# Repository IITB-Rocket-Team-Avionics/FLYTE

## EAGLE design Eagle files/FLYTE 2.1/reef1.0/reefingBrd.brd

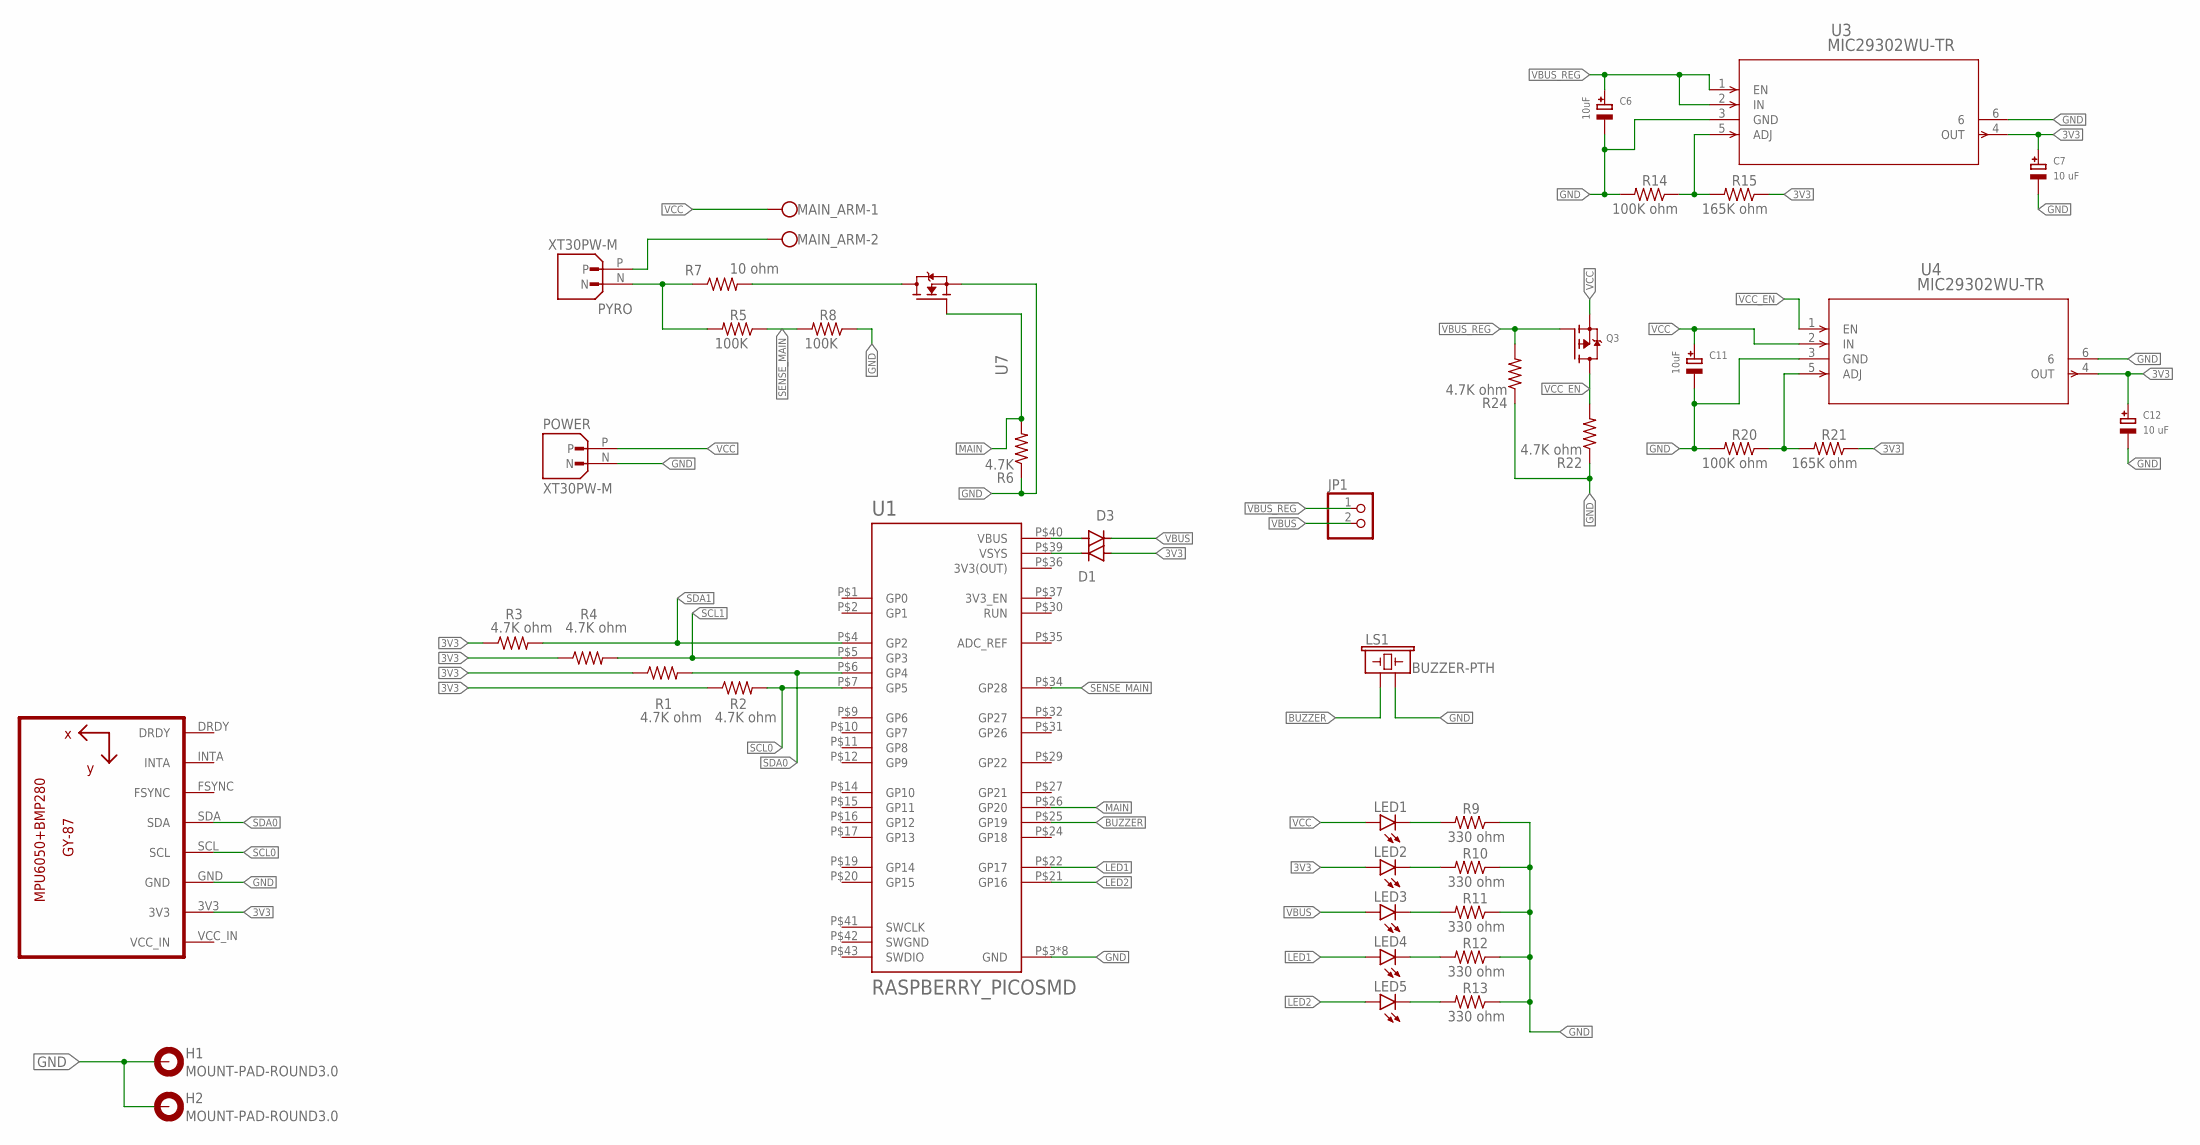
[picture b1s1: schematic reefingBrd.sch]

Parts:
C6, C11: 10uF; EIA3216-18/A-W
C7, C12: 10 uF; EIA3216-18/A-W
D1, D3: 1N4004; DO41-10
H1, H2: MOUNT-PAD-ROUND3.0; 3,0-PAD
JP1: PINHD-1X2; 1X02
LED1, LED2, LED3, LED4, LED5: LEDCHIPLED_1206; CHIPLED_1206
LS1: BUZZER-PTH; BUZZER-12MM
MAIN_ARM: W237-102
POWER: XT30PW-M; AMASS_XT30PW-M
PYRO: XT30PW-M; AMASS_XT30PW-M
Q3: MOSFET-PWIDE; SOT23-WIDE
R1, R2, R3, R4, R22, R24: 4.7K ohm; R0805
R5, R8: 100K; R0805
R6: 4.7K; R0805
R7: 10 ohm; 0207/10
R9, R10, R11, R12, R13: 330 ohm; R0805
R14, R20: 100K ohm; R0805
R15, R21: 165K ohm; R0805
U1: RASPBERRY_PICOSMD; PICO-PKG-SMD
U2: GY-521MPU6050; GY-521
U3, U4: MIC29302WU-TR; TO-263-5_MCH
U7: IRF540NPBF; TO254P1054X469X1930-3

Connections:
3V3: C7.+, C12.+, D1.A, LED2.A, R1.1, R2.1, R3.1, R4.1, R15.1, R21.1, U2.3V3, U3.4 (OUT), U4.4 (OUT)
3V3(OUT): U1.P$36 (3V3(OUT))
BUZZER: LS1.+ (1), U1.P$25 (GP19)
GND: C6.-, C7.-, C11.-, C12.-, H1.B3,0, H2.B3,0, LS1.- (2), POWER.N, R6.1, R8.1, R9.1, R10.1, R11.1, R12.1, R13.1, R14.2, R20.2, R22.1, R24.1, U1.P$3 (GND), U1.P$8 (GND), U1.P$13 (GND), U1.P$18 (GND), U1.P$23 (GND), U1.P$28 (GND), U1.P$33 (GND), U1.P$38 (GND), U2.GND, U3.3 (GND), U3.6, U4.3 (GND), U4.6, U7.3 (S)
LED1: LED4.A, U1.P$22 (GP17)
LED2: LED5.A, U1.P$21 (GP16)
MAIN: R6.2, U1.P$26 (GP20), U7.1 (G)
unnamed: D1.C, U1.P$39 (VSYS)
unnamed: D3.A, U1.P$40 (VBUS)
unnamed: R20.1, R21.2, U4.5 (ADJ)
unnamed: PYRO.N, R5.2, R7.1
unnamed: R7.2, U7.2 (D)
unnamed: MAIN_ARM.2, PYRO.P
unnamed: R14.1, R15.2, U3.5 (ADJ)
unnamed: LED1.C, R9.2
unnamed: LED2.C, R10.2
unnamed: LED3.C, R11.2
unnamed: LED4.C, R12.2
unnamed: LED5.C, R13.2
SCL0: R2.2, U1.P$7 (GP5), U2.SCL
SCL1: R4.2, U1.P$5 (GP3)
SDA0: R1.2, U1.P$6 (GP4), U2.SDA
SDA1: R3.2, U1.P$4 (GP2)
SENSE_MAIN: R5.1, R8.2, U1.P$34 (GP28)
SWGND: U1.P$42 (SWGND)
VBUS: D3.C, JP1.2, LED3.A
VBUS_REG: C6.+, JP1.1, Q3.1 (G), R24.2, U3.1 (EN), U3.2 (IN)
VCC: C11.+, LED1.A, MAIN_ARM.1, POWER.P, Q3.2 (S), U4.2 (IN)
VCC_EN: Q3.3 (D), R22.2, U4.1 (EN)

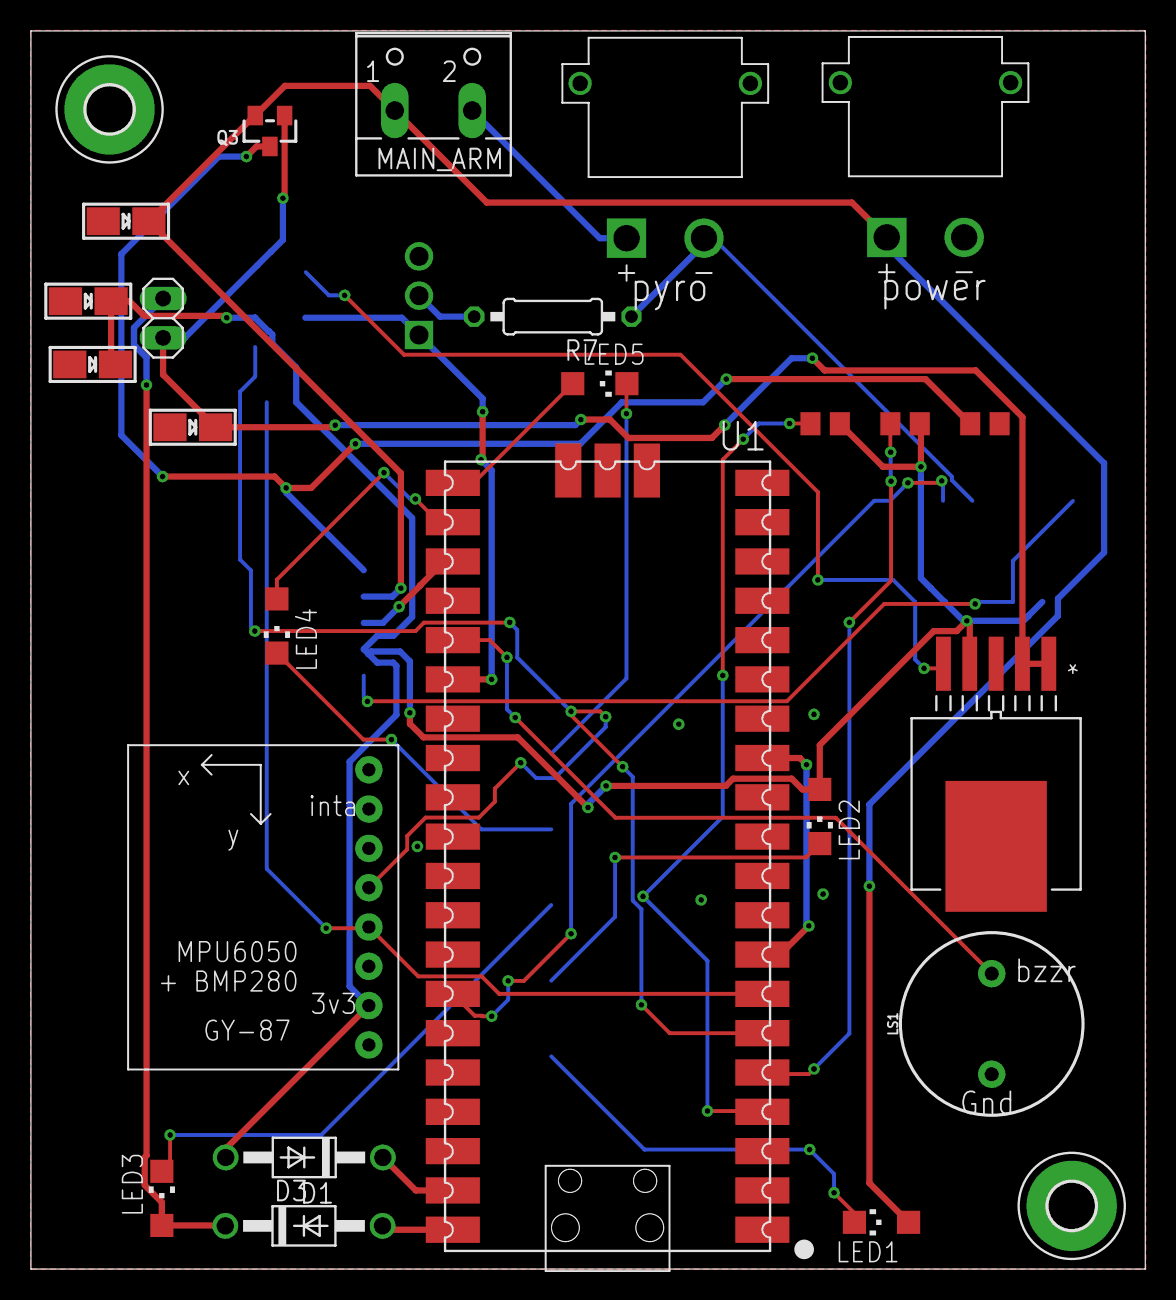
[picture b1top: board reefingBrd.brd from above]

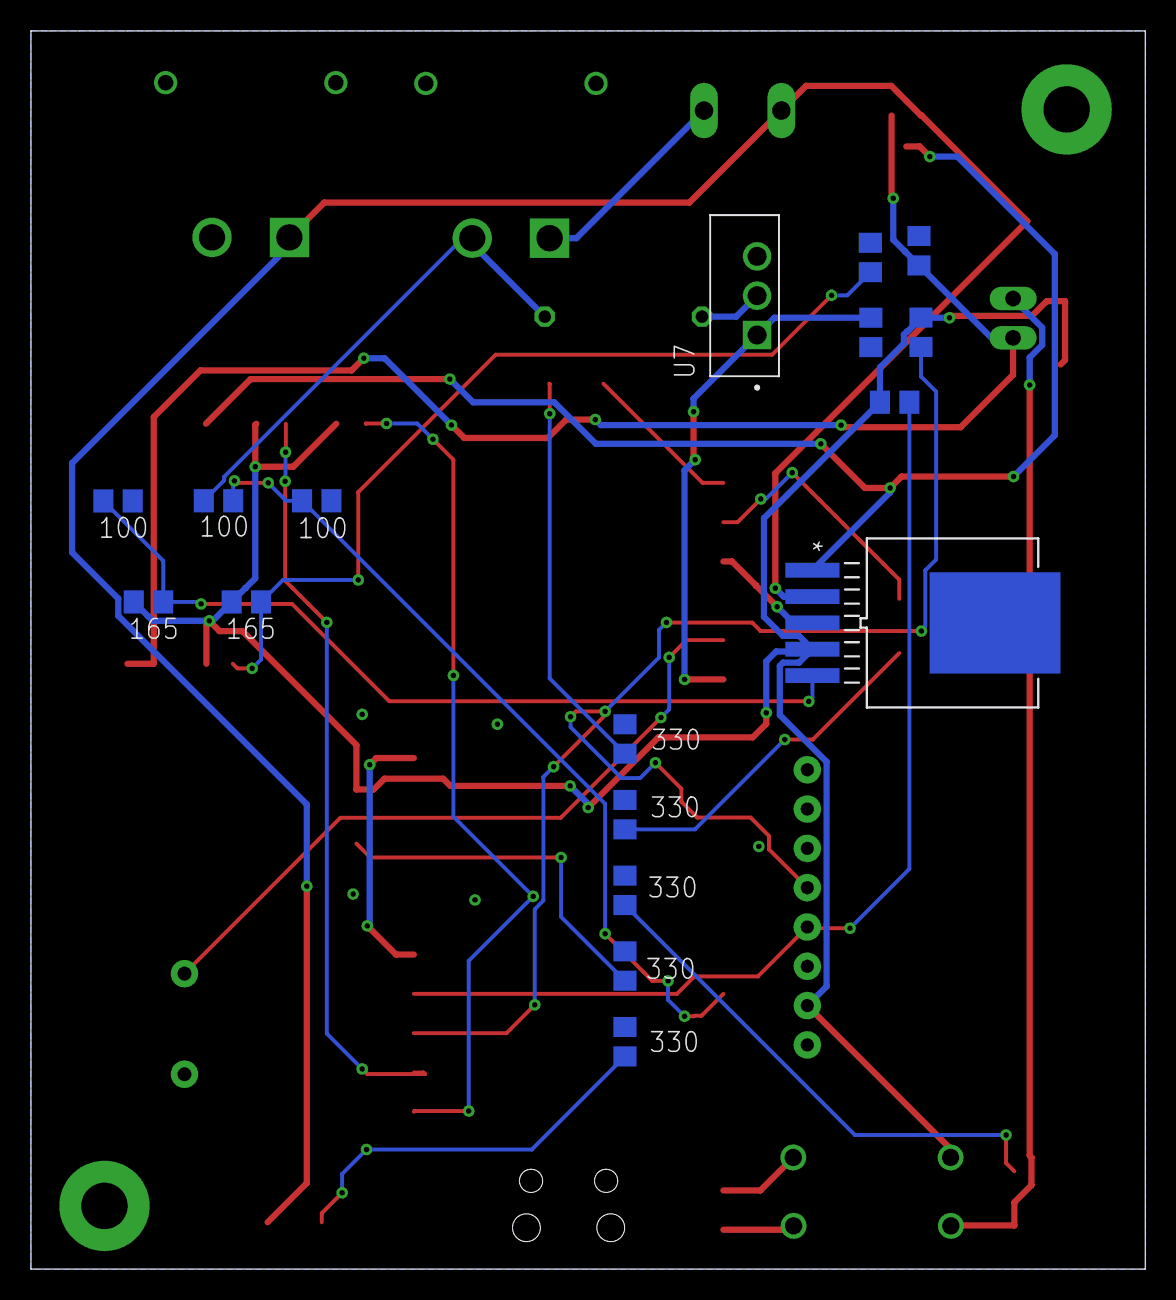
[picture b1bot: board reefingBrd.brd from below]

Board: 2 copper layers, 72.0 x 80.0 mm, 43 parts (17 on the bottom side), 27 nets.

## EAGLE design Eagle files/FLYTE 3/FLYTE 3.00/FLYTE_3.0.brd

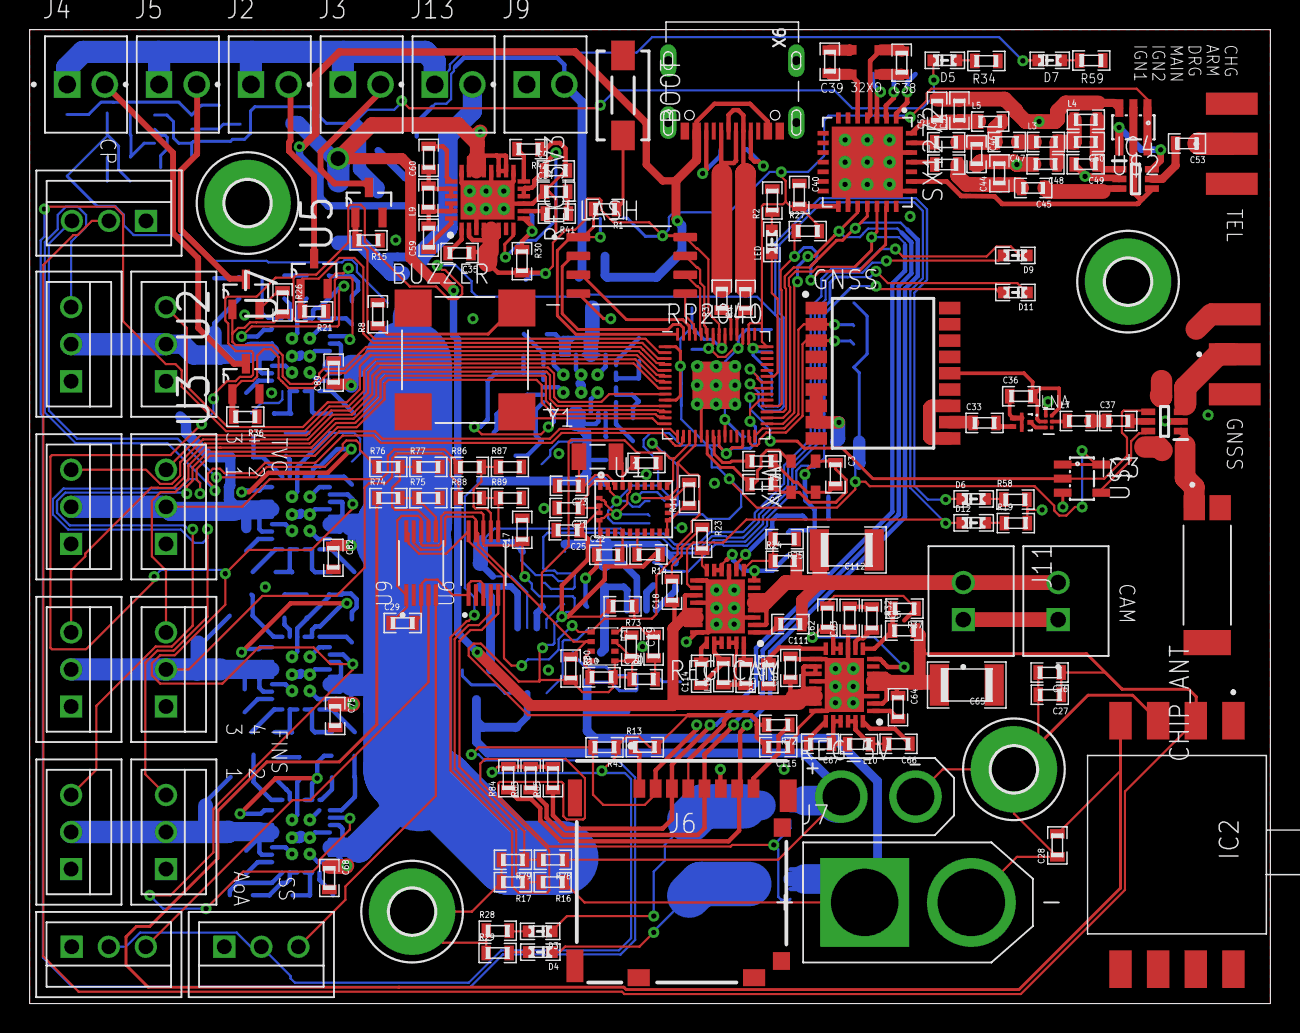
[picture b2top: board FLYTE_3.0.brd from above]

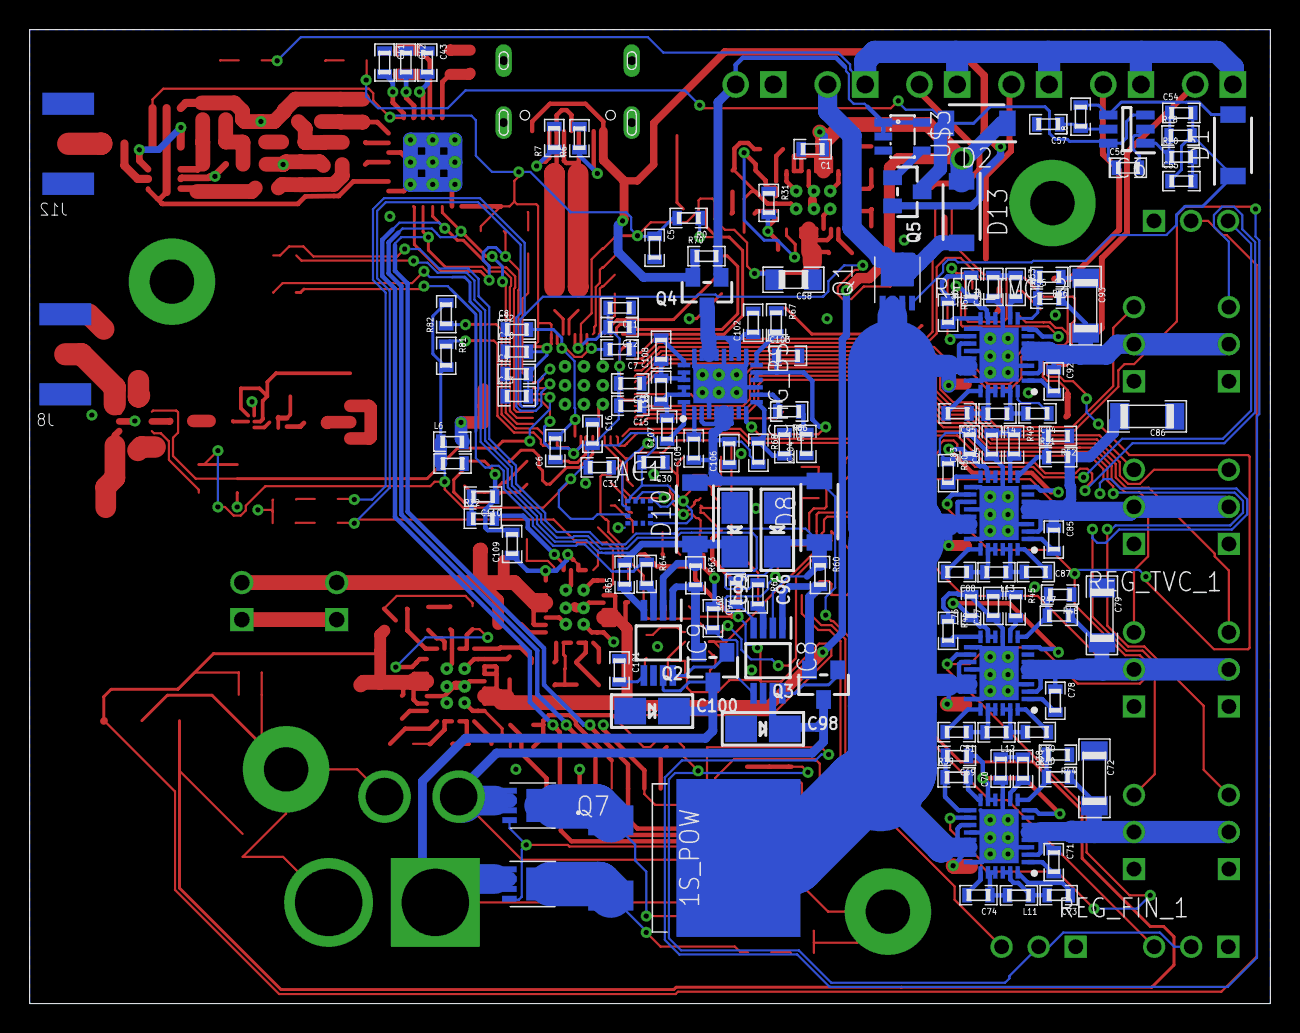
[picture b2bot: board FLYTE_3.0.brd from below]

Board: 2 copper layers, 83.7 x 65.7 mm, 307 parts (129 on the bottom side), 222 nets.

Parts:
1S_POW: V60D60C-M3_I; V60D60CM3I
32XO: ASE
AC1: KX134-1211; KX1341211
AOA: 03-JST-B3B-XH-A; B3B-XH
BOOT: DTSM-3
BUZZER: BUZZER; CUI_CMT-8530S-SMT
C1, C18, C61, C68, C75, C82, C89, C102, C106: 10 uF; 0603
C2, C3, C38, C39: 24 pF; 0603
C4, C57, C62, C69, C76, C83, C90, C103, C109: 4.7 uF; 0603
C5, C6, C7, C9, C11, C12, C13, C14, C15, C16, C19, C20, C21, C22, C25, C40, C41, C42, C43: 100 nF; 0603
C8, C10, C26, C55, C56, C115: 1 uF; 0603
C17, C29, C30, C31, C97, C101: 0.1 uF; 0603
C23, C24: 25 pF; 0603
C27, C32, C51: 10 nF; 0603
C28: 470 pF; 0603
C33, C37: 120 pF; 0603
C34: 3.3 nF; 0603
C35, C64, C71, C78, C85, C92, C105, C111: 22 nF; 0603
C36: 1 nF; 0603
C44, C49: 3.3 pF; 0603
C45, C52, C53: 47 pF; 0603
C46, C48: 8.2 pF; 0603
C47: 22 pF; 0603
C50: 1.5 pF; 0603
C54: 10 pF; 0603
C58: 100 uF; 0805
C59, C60, C66, C67, C73, C74, C80, C81, C87, C88, C94, C95, C107, C108, C113, C114: 0.22 uF; 0603
C63, C70, C77, C84, C91, C110: 1.8 nF; 0603
C65: 220 uF; 1210
C72, C79, C86, C93: 100 uF; 1206
C96, C98, C99, C100: 10uF; EIA3216-18/A-W
C104: 1.2 nF; 0603
C112: 100 uF; 1210
CHG_BST: LT3120JV#PBF; QFN50P400X500X83-29N
CHIP_ANT: W3010; XCVR_W3010
D1, D2, D8, D10, D13: RSX501LAM20TR; SODFL4725X105N
D3, D4, D5, D6, D7, D9, D11, D12: 0603.LED
FIN_1, FIN_2, FIN_3, FIN_4: 03-JST-B3B-XH-A; B3B-XH
FLASH: W25Q128JVSIQ; SOIC127P790X216-8N
GNSS: TESEO-LIV3F; SON110P970X1010X230-18N
H1, H2, H3, H4: MOUNT-PAD-ROUND3.0; 3,0-PAD
IC1: BMP280
IC2: MPXV5100DP
IC3, IC4: AS179-92LF; SOT65P220X100-6N
IC6: MAX8574EUT+T; SOT95P280X145-6N
IC8: MCP73843-420I_MS; SOP65P490X110-8N
IC9: MCP73844-840I_MS; SOP65P490X110-8N
J2, J3, J4, J5, J9, J13: 282834-2; TE_282834-2
J6: 503182-1852; 5031821852
J7: XT60-M; AMASS_XT60-M
J8, J12: CON-SMA-EDGE-S; RFSOLUTIONS_CON-SMA-EDGE-S
J10, J11: B2B-XH-A(LF)(SN); JST_B2B-XH-A(LF)(SN)
L1: 10 nH; 0603
L2: 2.7 nH; 0603
L3, L4, L7: 5.6 nH; 0603
L5: 33 nH; 0603
L6: 27 nH; 0603
L8: 22 uH; 0603
L9, L10, L11, L12, L13, L14, L15, L16: 4.7 uH; 0603
LED: 0603.LED
LNA: BGA725L6; AMP_BGA725L6E6327FTSA1
MOTOR: 03-JST-B3B-XH-A; B3B-XH
Q1, Q6, Q7: SI7625DN-T1-GE3; SIS862DNT1GE3
Q2, Q3, Q4, Q5: SOT23-WIDE
R0, R9, R10, R13, R15, R20, R21, R26, R27, R36, R43, R70, R72, R73, R80, R81, R82, R83, R84, R85: 10k ohm; 0603
R1, R5: 1k ohm; 0603
R2, R19, R58: 60 ohm; 0603
R3, R4: 27.4 ohm; 0603
R6, R7: 5.1k ohm; 0603
R8: 100 ohm; 0603
R11, R14: 10 kohm; 0603
R16: 412k ohm; 0603
R17, R25, R31, R37, R62, R65, R66, R69, R75, R77, R79, R87, R89: 100k ohm; 0603
R18: 137k ohm; 0603
R22, R32, R38, R45, R49, R53: 46.4k ohm; 0603
R23, R33, R39, R42, R46, R50, R54, R67, R86, R88: 158k ohm; 0603
R24, R35: 523k ohm; 0603
R28: 105 ohm; 0603
R29, R59: 315 ohm; 0603
R30: 316k ohm; 0603
R34, R61, R64: 158 ohm; 0603
R40, R47, R51, R55: 402k ohm; 0603
R41: 21k ohm; 0603
R44, R48, R52, R56: 50k ohm; 0603
R60, R63: 0.1 ohm; 0603
R68: 1.3M ohm; 0603
R74: 36.5k ohm; 0603
R76: 43k ohm; 0603
R78: 28k ohm; 0603
REG_3V3, REG_5V: LT3120JV#PBF; QFN50P400X500X83-29N
REG_CAM: LT3120JV#PBF; QFN50P400X500X83-29N
REG_FIN_1, REG_FIN_2: LT3120JV#PBF; QFN50P400X500X83-29N
REG_TVC_1, REG_TVC_2: LT3120JV#PBF; QFN50P400X500X83-29N
RP2040: RP2040-QFN56; RP2040-QFN-56
SAW: SAW_FILTER; FIL_AFS14A04-1575.42-T3
SS: 03-JST-B3B-XH-A; B3B-XH
SX1272: SX1272IMLTRT; QFN65P600X600X100-29N
TVC_1, TVC_2, TVC_3, TVC_4: 03-JST-B3B-XH-A; B3B-XH
U1: BNO055; LGA28R50P4X10_380X520X100
U2, U3, U5, U7: CJ3400; SOT91P240X120-3N
U6, U9: ADS1115IDGSR; SOP50P490X110-10N
U$1, U$2, U$3: SN74LVC1G04DBVR; SOT23-5
U$11: XT30UPB-M
X6: USB Type C; USB_C_CUSB31-CFM2AX-01-X
XTAL: ASE
Y1: FC-135_32.7680KA-A0; XTAL_FC-135_32.7680KA-A0

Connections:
1S_ADC: R78.2, R79.1, U6.5
1S_POW: 1S_POW.1, D3.P$1, Q7.5, Q7.6, Q7.7, Q7.8, Q7.9, Q7.10, Q7.11
1V1: C6.2, C7.2, C8.2, RP2040.23, RP2040.45, RP2040.50
2S_ADC: R16.2, R17.1, U6.4
2S_POW: 1S_POW.2, D4.P$1, Q6.5, Q6.6, Q6.7, Q6.8, Q6.9, Q6.10, Q6.11
3V3: AC1.1, AC1.3, AC1.7, AC1.10, AOA.P$2, C5.1, C9.2, C10.2, C11.2, C12.2, C13.2, C14.2, C15.2, C16.2, C17.1, C19.2, C20.1, C21.1, C25.1, C29.1, C30.2, C31.2, C32.2, C35.1, C40.2, C41.2, C58.2, C115.2, FLASH.8, IC1.6, IC1.8, J6.4, L6.1, R0.2, R10.2, R13.2, R14.1, R27.2, R30.2, R43.1, R72.2, R73.2, R80.2, R81.2, R82.2, R83.2, R84.2, R85.2, REG_3V3.2, REG_3V3.4, REG_3V3.5, REG_3V3.6, RP2040.1, RP2040.10, RP2040.22, RP2040.26, RP2040.33, RP2040.42, RP2040.44, RP2040.48, RP2040.49, SS.P$2, SX1272.1, SX1272.15, U1.3, U1.4, U1.28, U6.8, U9.1, U9.8, U$1.1, U$1.5, U$2.1, U$2.5
5V: C26.1, C27.1, C64.1, C65.2, IC2.2, MOTOR.P$2, R35.2, REG_5V.2, REG_5V.4, REG_5V.5, REG_5V.6
AIN2: R88.2, R89.1, U6.6
AIN3: R86.2, R87.1, U6.7
AOA_ADC: AOA.P$3, U9.4
BC: J9.2, Q4.1, R70.2, U$3.1, U$3.2, U$3.5
BUZZER: BUZZER.P, RP2040.14
CAM: D12.P$1, REG_CAM.16, RP2040.35
CC1: R7.1, X6.A5
CC2: R6.1, X6.B5
CSB: IC1.2, R10.1
CS_SD: J6.2, R43.2, RP2040.7
CS_SX: R27.1, RP2040.32, SX1272.20
CTRL: D6.P$1, REG_FIN_1.16, REG_FIN_2.16, REG_TVC_1.16, REG_TVC_2.16, RP2040.36
D+: R3.2, X6.A6, X6.B6
D-: R4.2, X6.A7, X6.B7
DROGUE: R15.2, RP2040.2, U5.1
F1: R30.1, R31.2, REG_3V3.9
F2: R35.1, R37.2, REG_5V.9
F3: R40.1, R44.2, REG_FIN_1.9
F4: R47.1, R48.2, REG_FIN_2.9
F5: R51.1, R52.2, REG_TVC_1.9
F6: R55.1, R56.2, REG_TVC_2.9
F7: CHG_BST.9, R68.1, R69.2
F8: R24.1, R25.2, REG_CAM.9
FB: C54.1, IC6.1, R18.1, R20.1
FIN_1: FIN_1.P$3, RP2040.13
FIN_2: FIN_2.P$3, RP2040.15
FIN_3: FIN_3.P$3, RP2040.11
FIN_4: FIN_4.P$3, RP2040.12
GND: 32XO.2, 32XO.4, AC1.4, AC1.8, AC1.9, AOA.P$1, BOOT.1, C1.2, C2.1, C3.1, C4.2, C5.2, C6.1, C7.1, C8.1, C9.1, C10.1, C11.1, C12.1, C13.1, C14.1, C15.1, C16.1, C17.2, C18.2, C19.1, C20.2, C21.2, C22.1, C23.2, C24.2, C25.2, C26.2, C27.2, C28.1, C29.2, C30.1, C31.1, C32.1, C34.1, C36.1, C38.1, C39.1, C40.1, C41.1, C42.1, C43.1, C44.2, C46.2, C48.2, C49.2, C51.2, C52.2, C55.2, C56.2, C57.2, C58.1, C61.2, C62.2, C63.1, C65.1, C68.2, C69.2, C70.1, C72.1, C75.2, C76.2, C77.1, C79.1, C82.2, C83.2, C84.1, C86.1, C89.2, C90.2, C91.1, C93.1, C96.-, C97.1, C98.-, C99.-, C100.-, C101.1, C102.2, C103.2, C104.1, C106.1, C109.2, C110.1, C112.1, C115.1, CHG_BST.3, CHG_BST.11, CHG_BST.15, CHG_BST.18, CHG_BST.22, CHG_BST.29, CHG_BST.P$1, CHG_BST.P$2, CHG_BST.P$3, CHG_BST.P$4, CHG_BST.P$5, CHG_BST.P$6, CHIP_ANT.2, CHIP_ANT.3, FIN_1.P$1, FIN_2.P$1, FIN_3.P$1, FIN_4.P$1, FLASH.4, GNSS.1, GNSS.10, GNSS.12, H1.B3,0, H2.B3,0, H3.B3,0, H4.B3,0, IC1.1, IC1.7, IC2.3, IC3.2, IC4.2, IC6.2, IC8.6, IC9.6, J6.6, J7.N, J8.G1, J8.G2, J8.G3, J8.G4, J9.1, J10.1, J11.1, J12.G1, J12.G2, J12.G3, J12.G4, LNA.1, LNA.4, MOTOR.P$1, R2.2, R6.2, R7.2, R8.2, R9.1, R11.1, R15.1, R17.2, R19.2, R20.2, R21.1, R23.1, R25.1, R26.1, R28.1, R29.1, R31.1, R33.1, R34.1, R36.1, R37.1, R39.1, R42.1, R44.1, R46.1, R48.1, R50.1, R52.1, R54.1, R56.1, R58.2, R59.2, R67.1, R69.1, R75.2, R77.2, R79.2, R87.2, R89.2, REG_3V3.3, REG_3V3.11, REG_3V3.15, REG_3V3.18, REG_3V3.22, REG_3V3.29, REG_3V3.P$1, REG_3V3.P$2, REG_3V3.P$3, REG_3V3.P$4, REG_3V3.P$5, REG_3V3.P$6, REG_5V.3, REG_5V.11, REG_5V.15, REG_5V.18, REG_5V.22, REG_5V.29, REG_5V.P$1, REG_5V.P$2, REG_5V.P$3, REG_5V.P$4, REG_5V.P$5, REG_5V.P$6, REG_CAM.3, REG_CAM.11, REG_CAM.15, REG_CAM.18, REG_CAM.22, REG_CAM.29, REG_CAM.P$1, REG_CAM.P$2, REG_CAM.P$3, REG_CAM.P$4, REG_CAM.P$5, REG_CAM.P$6, REG_FIN_1.3, REG_FIN_1.11, REG_FIN_1.15, REG_FIN_1.18, REG_FIN_1.22, REG_FIN_1.29, REG_FIN_1.P$1, REG_FIN_1.P$2, REG_FIN_1.P$3, REG_FIN_1.P$4, REG_FIN_1.P$5, REG_FIN_1.P$6, REG_FIN_2.3, REG_FIN_2.11, REG_FIN_2.15, REG_FIN_2.18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
GPS_RX: GNSS.3, R81.1, RP2040.27
GPS_TX: GNSS.2, R82.1, RP2040.28
IGN1: R36.2, RP2040.5, U3.1
IGN2: R26.2, RP2040.4, U2.1
LED: LED.P$1, RP2040.37
MAIN: R21.2, RP2040.3, U7.1
MISO: J6.7, R84.1, RP2040.31, SX1272.18
MOS: D13.2, J13.2, Q1.5, Q1.6, Q1.7, Q1.8, Q1.9, Q1.10, Q1.11
MOSI: J6.3, R85.1, RP2040.30, SX1272.19
unnamed: D1.2, IC6.4, L8.2
unnamed: LED.P$2, R2.1
unnamed: C3.2, R5.1, XTAL.1
unnamed: C33.1, GNSS.11
unnamed: BUZZER.N, R8.1
unnamed: D12.P$2, R19.1
unnamed: J6.1, R13.1
unnamed: GNSS.6, GNSS.7, GNSS.8, L6.2
unnamed: C22.2, U1.9
unnamed: R11.2, U1.17
unnamed: J6.8, R72.1
unnamed: R74.2, R75.1, U9.6
unnamed: R14.2, U1.11
unnamed: R22.2, REG_CAM.10
unnamed: R76.2, R77.1, U9.7
unnamed: C110.2, R22.1
unnamed: C59.2, L9.1, REG_3V3.26, REG_3V3.27
unnamed: L7.1, LNA.5
unnamed: C37.1, L7.2
unnamed: C33.2, SAW.A
unnamed: LNA.3, SAW.C
unnamed: C37.2, IC3.5
unnamed: CHIP_ANT.1, IC3.1
unnamed: IC3.3, J8.1
unnamed: C42.2, SX1272.2
unnamed: C43.2, SX1272.3
unnamed: C44.1, C45.2, L1.2
unnamed: C45.1, IC4.3
unnamed: L2.1, SX1272.27
unnamed: L1.1, SX1272.25
unnamed: C46.1, C47.2, L2.2, L5.2
unnamed: C47.1, L3.1
unnamed: C48.1, C50.2, L3.2, L4.1
unnamed: C49.1, C50.1, IC4.1, L4.2
unnamed: C51.1, C52.1, L5.1, SX1272.28
unnamed: C53.2, IC4.5
unnamed: C53.1, J12.1
unnamed: C99.+, D10.1, D11.P$1, IC9.2, R63.1, R65.2
unnamed: R41.2, REG_3V3.10
unnamed: IC9.1, Q2.2, R63.2
unnamed: C34.2, R41.1
unnamed: R42.2, REG_3V3.14
unnamed: C35.2, REG_3V3.1
unnamed: C60.1, L9.2, REG_3V3.24, REG_3V3.25
unnamed: C59.1, REG_3V3.28
unnamed: C57.1, IC6.5, L8.1
unnamed: D3.P$2, R28.2
unnamed: C54.2, C55.1, D1.1, Q1.4, R18.2
unnamed: D4.P$2, R29.2
unnamed: D5.P$2, R34.2
unnamed: C60.2, REG_3V3.23
unnamed: R32.2, REG_5V.10
unnamed: C63.2, R32.1
unnamed: R33.2, REG_5V.14
unnamed: C64.2, REG_5V.1
unnamed: C66.2, L10.1, REG_5V.26, REG_5V.27
unnamed: C67.1, L10.2, REG_5V.24, REG_5V.25
unnamed: C66.1, REG_5V.28
unnamed: C67.2, REG_5V.23
unnamed: R38.2, REG_FIN_1.10
unnamed: C70.2, R38.1
unnamed: R39.2, REG_FIN_1.14
unnamed: C71.2, REG_FIN_1.1
unnamed: C73.2, L11.1, REG_FIN_1.26, REG_FIN_1.27
unnamed: C74.1, L11.2, REG_FIN_1.24, REG_FIN_1.25
unnamed: C73.1, REG_FIN_1.28
unnamed: C74.2, REG_FIN_1.23
unnamed: R45.2, REG_FIN_2.10
unnamed: C77.2, R45.1
unnamed: R46.2, REG_FIN_2.14
unnamed: C78.2, REG_FIN_2.1
unnamed: C80.2, L12.1, REG_FIN_2.26, REG_FIN_2.27
unnamed: C81.1, L12.2, REG_FIN_2.24, REG_FIN_2.25
unnamed: C80.1, REG_FIN_2.28
unnamed: C81.2, REG_FIN_2.23
unnamed: R49.2, REG_TVC_1.10
unnamed: C84.2, R49.1
unnamed: R50.2, REG_TVC_1.14
unnamed: C85.2, REG_TVC_1.1
unnamed: C87.2, L13.1, REG_TVC_1.26, REG_TVC_1.27
unnamed: C88.1, L13.2, REG_TVC_1.24, REG_TVC_1.25
unnamed: C87.1, REG_TVC_1.28
unnamed: C88.2, REG_TVC_1.23
unnamed: R53.2, REG_TVC_2.10
unnamed: C91.2, R53.1
unnamed: R54.2, REG_TVC_2.14
unnamed: C92.2, REG_TVC_2.1
unnamed: C94.2, L14.1, REG_TVC_2.26, REG_TVC_2.27
unnamed: C95.1, L14.2, REG_TVC_2.24, REG_TVC_2.25
unnamed: C94.1, REG_TVC_2.28
unnamed: C95.2, REG_TVC_2.23
unnamed: D6.P$2, R58.1
unnamed: D7.P$2, R59.1
unnamed: C96.+, D8.1, D9.P$1, IC8.2, R60.1, R62.2
unnamed: IC8.1, Q3.2, R60.2
unnamed: D9.P$2, R61.1
unnamed: IC8.3, R61.2
unnamed: IC8.4, R62.1
unnamed: IC8.8, Q3.1
unnamed: D11.P$2, R64.1
unnamed: C97.2, IC8.5
unnamed: IC9.3, R64.2
unnamed: IC9.4, R65.1
unnamed: IC9.8, Q2.1
unnamed: C101.2, IC9.5
unnamed: CHG_BST.10, R66.2
unnamed: C104.2, R66.1
unnamed: CHG_BST.14, R67.2
unnamed: C105.2, CHG_BST.1
unnamed: C107.2, CHG_BST.26, CHG_BST.27, L15.1
unnamed: C108.1, CHG_BST.24, CHG_BST.25, L15.2
unnamed: C107.1, CHG_BST.28
unnamed: C108.2, CHG_BST.23
unnamed: R23.2, REG_CAM.14
unnamed: C111.2, REG_CAM.1
unnamed: Q5.1, U$3.4
unnamed: C113.2, L16.1, REG_CAM.26, REG_CAM.27
unnamed: C114.1, L16.2, REG_CAM.24, REG_CAM.25
unnamed: C113.1, REG_CAM.28
unnamed: C114.2, REG_CAM.23
N_RXTX: IC4.6, U$2.4
N_S: IC3.6, U$1.4
P1: C4.1, REG_3V3.8, REG_3V3.12, REG_3V3.13
P2: C62.1, REG_5V.8, REG_5V.12, REG_5V.13
P3: C69.1, REG_FIN_1.8, REG_FIN_1.12, REG_FIN_1.13
P4: C76.1, REG_FIN_2.8, REG_FIN_2.12, REG_FIN_2.13
P5: C83.1, REG_TVC_1.8, REG_TVC_1.12, REG_TVC_1.13
P6: C90.1, REG_TVC_2.8, REG_TVC_2.12, REG_TVC_2.13
P7: C103.1, CHG_BST.8, CHG_BST.12, CHG_BST.13
P8: C109.1, REG_CAM.8, REG_CAM.12, REG_CAM.13
PYRO_DROGUE: J3.2, U5.3
PYRO_IGN1: J4.2, U3.3
PYRO_IGN2: J5.2, U2.3
PYRO_MAIN: J2.2, U7.3
QSPI_SCLK: FLASH.6, RP2040.52
QSPI_SD0: FLASH.5, RP2040.53
QSPI_SD1: FLASH.2, RP2040.55
QSPI_SD2: FLASH.3, RP2040.54
QSPI_SD3: FLASH.7, RP2040.51
QSPI_SS: FLASH.1, R0.1, R1.2, RP2040.56
RXTX: IC4.4, SX1272.23, U$2.2
S: IC3.4, RP2040.34, U$1.2
SCK: J6.5, R83.1, RP2040.29, SX1272.17
SCL: AC1.12, IC1.4, R73.1, RP2040.18, U1.19, U6.10, U9.10
SDA: AC1.2, IC1.3, R80.1, RP2040.17, U1.20, U6.9, U9.9
SDO: IC1.5, R9.2
SS_ADC: SS.P$3, U9.5
TVC_1: RP2040.9, TVC_1.P$3
TVC_2: RP2040.8, TVC_2.P$3
TVC_3: RP2040.16, TVC_3.P$3
TVC_4: RP2040.6, TVC_4.P$3
USB+: Q4.2, Q5.2, R70.1, X6.A4B9, X6.B4A9
USB_BOOT: BOOT.2, R1.1
USB_BST: C105.1, C106.2, CHG_BST.2, CHG_BST.4, CHG_BST.5, CHG_BST.6, D8.2, D10.2, Q6.4, Q7.4, R68.2
USB_CHG: C102.1, CHG_BST.16, CHG_BST.17, CHG_BST.19, CHG_BST.20, CHG_BST.21, Q4.3
USB_DM: R4.1, RP2040.46
USB_DP: R3.1, RP2040.47
VBUS: C56.1, D2.2, D5.P$1, IC6.3, IC6.6, Q5.3
VCC: C1.1, C18.1, C61.1, D2.1, D13.1, REG_3V3.16, REG_3V3.17, REG_3V3.19, REG_3V3.20, REG_3V3.21, REG_5V.16, REG_5V.17, REG_5V.19, REG_5V.20, REG_5V.21, REG_CAM.17, REG_CAM.19, REG_CAM.20, REG_CAM.21
VCC_CTRL: 1S_POW.3, C68.1, C75.1, C82.1, C89.1, Q1.1, Q1.2, Q1.3, REG_FIN_1.17, REG_FIN_1.19, REG_FIN_1.20, REG_FIN_1.21, REG_FIN_2.17, REG_FIN_2.19, REG_FIN_2.20, REG_FIN_2.21, REG_TVC_1.17, REG_TVC_1.19, REG_TVC_1.20, REG_TVC_1.21, REG_TVC_2.17, REG_TVC_2.19, REG_TVC_2.20, REG_TVC_2.21
VCC_PYRO: D7.P$1, J2.1, J3.1, J4.1, J5.1, J13.1
VCC_RF: C36.2, GNSS.14, LNA.2, LNA.6
VOLT_DP: C28.2, IC2.4, R74.1
VOLT_MOTOR: MOTOR.P$3, R76.1
V_CAM: C111.1, C112.2, J10.2, J11.2, R24.2, REG_CAM.2, REG_CAM.4, REG_CAM.5, REG_CAM.6
V_FIN_1: C71.1, C72.2, FIN_1.P$2, FIN_2.P$2, R40.2, REG_FIN_1.2, REG_FIN_1.4, REG_FIN_1.5, REG_FIN_1.6
V_FIN_2: C78.1, C79.2, FIN_3.P$2, FIN_4.P$2, R47.2, R88.1, REG_FIN_2.2, REG_FIN_2.4, REG_FIN_2.5, REG_FIN_2.6
V_TVC_1: C85.1, C86.2, R51.2, R86.1, REG_TVC_1.2, REG_TVC_1.4, REG_TVC_1.5, REG_TVC_1.6, TVC_1.P$2, TVC_2.P$2
V_TVC_2: C92.1, C93.2, R55.2, REG_TVC_2.2, REG_TVC_2.4, REG_TVC_2.5, REG_TVC_2.6, TVC_3.P$2, TVC_4.P$2
XIN: C2.2, RP2040.20, XTAL.3
XIN1: 32XO.3, C38.2, SX1272.4
XIN32: C23.1, U1.27, Y1.1
XOUT: R5.2, RP2040.21
XOUT1: 32XO.1, C39.2, SX1272.5
XOUT32: C24.1, U1.26, Y1.2
XT30+: C98.+, IC8.7, Q3.3, Q7.1, Q7.2, Q7.3, R78.1, U$11.P$1
XT60+: C100.+, IC9.7, J7.P, Q2.3, Q6.1, Q6.2, Q6.3, R16.1

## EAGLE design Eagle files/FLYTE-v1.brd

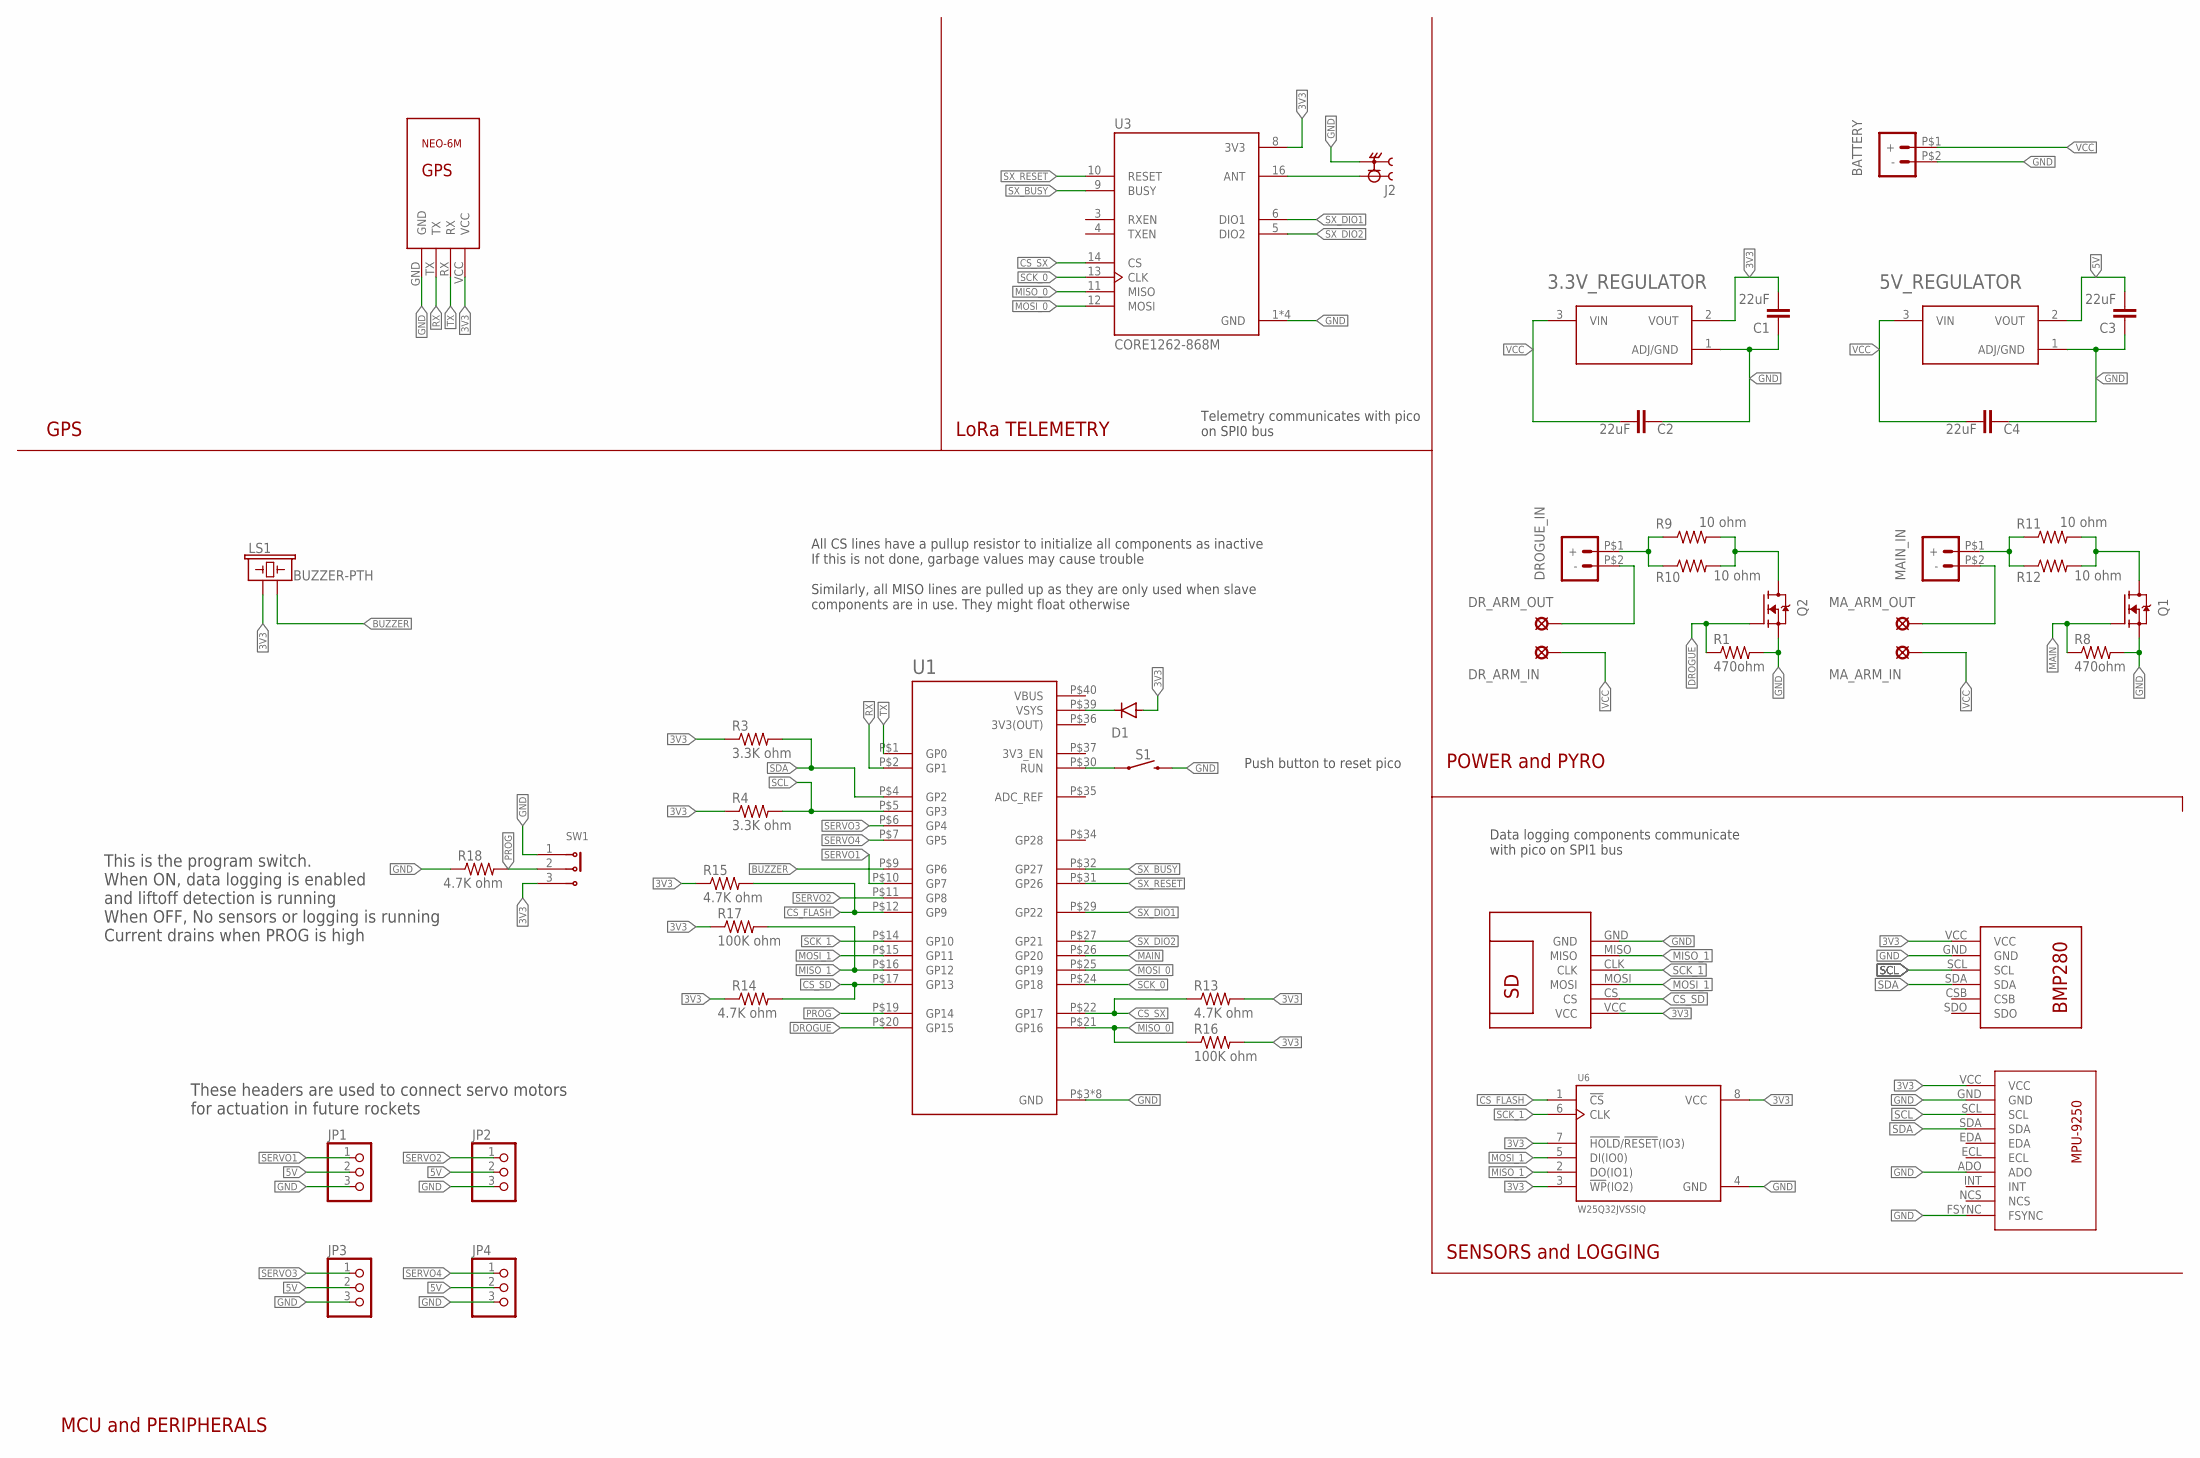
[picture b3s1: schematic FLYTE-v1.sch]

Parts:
3.3V_REGULATOR, 5V_REGULATOR: AMS1117-3.3; SOT229P700X180-4N
BATTERY: XT30UPB-M
C1, C2, C3, C4: 22uF; 0805
D1: 1N4004; DO41-10
DROGUE_IN: XT30UPB-M
DR_ARM_IN: LSP10
DR_ARM_OUT: LSP10
J2: CONSMA002; LINX_CONSMA002
JP1, JP2, JP3, JP4: PINHD-1X3; 1X03
LS1: BUZZER-PTH; BUZZER-12MM
MAIN_IN: XT30UPB-M
MA_ARM_IN: LSP10
MA_ARM_OUT: LSP10
Q1, Q2: IRF540NPBF; TO254P1054X469X1930-3
R1, R8: 470ohm; R0805
R3, R4: 3.3K ohm; R0805
R9, R10, R11, R12: 10 ohm; 0207/10
R13, R14, R15, R18: 4.7K ohm; R0805
R16, R17: 100K ohm; R0805
S1: MOMENTARY-SWITCH-SPST-PTH-6.0MM; TACTILE_SWITCH_PTH_6.0MM
SW1: 1825159-1; SW_1825159-1
U1: RASPBERRY_PICO-NO_DEBUG; PICO-PKG-NO_DEBUG
U3: CORE1262-868M; XCVR_CORE1262-868M
U6: W25Q32JVSSIQ; SOIC127P790X216-8N
U$1: BMP280
U$2: GY-9250
U$3: SDREADER
U$4: NEO-6M

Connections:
3V3: 3.3V_REGULATOR.2 (VOUT), C1.2, D1.A, LS1.+ (1), R3.1, R4.1, R13.2, R14.1, R15.1, R16.2, R17.1, SW1.3, U3.8 (3V3), U6.3 (!WP!(IO2)), U6.7 (!HOLD!/!RESET!(IO3)), U6.8 (VCC), U$1.VCC, U$2.VCC, U$3.VCC, U$4.VCC
3V3(OUT): U1.P$36 (3V3(OUT))
5V: 5V_REGULATOR.2 (VOUT), C3.2, JP1.2, JP2.2, JP3.2, JP4.2
ANT: J2.1, U3.16 (ANT)
BUZZER: LS1.- (2), U1.P$9 (GP6)
CS_FLASH: R15.2, U1.P$12 (GP9), U6.1 (!CS)
CS_SD: R14.2, U1.P$17 (GP13), U$3.CS
CS_SX: R13.1, U1.P$22 (GP17), U3.14 (CS)
DROGUE: Q2.1 (G), R1.1, U1.P$20 (GP15)
GND: 3.3V_REGULATOR.1 (ADJ/GND), 5V_REGULATOR.1 (ADJ/GND), BATTERY.P$2 (-), C1.1, C2.1, C3.1, C4.1, J2.S1 (2), J2.S2 (2), J2.S3 (2), J2.S4 (2), JP1.3, JP2.3, JP3.3, JP4.3, Q1.3 (S), Q2.3 (S), R1.2, R8.2, R18.1, S1.3 (2), SW1.1, U1.P$3 (GND), U1.P$8 (GND), U1.P$13 (GND), U1.P$18 (GND), U1.P$23 (GND), U1.P$28 (GND), U1.P$33 (GND), U1.P$38 (GND), U3.1 (GND), U3.2 (GND), U3.7 (GND), U3.15 (GND), U6.4 (GND), U$1.GND, U$2.ADO, U$2.FSYNC, U$2.GND, U$3.GND, U$4.GND
MAIN: Q1.1 (G), R8.1, U1.P$26 (GP20)
MISO_0: R16.1, U1.P$21 (GP16), U3.11 (MISO)
MISO_1: R17.2, U1.P$16 (GP12), U6.2 (DO(IO1)), U$3.MISO
MOSI_0: U1.P$25 (GP19), U3.12 (MOSI)
MOSI_1: U1.P$15 (GP11), U6.5 (DI(IO0)), U$3.MOSI
unnamed: D1.C, U1.P$39 (VSYS)
unnamed: DROGUE_IN.P$2 (-), DR_ARM_OUT.MP
unnamed: MAIN_IN.P$1 (+), R11.1, R12.1
unnamed: DROGUE_IN.P$1 (+), R9.1, R10.1
unnamed: S1.1, U1.P$30 (RUN)
unnamed: Q2.2 (D), R9.2, R10.2
unnamed: Q1.2 (D), R11.2, R12.2
unnamed: MAIN_IN.P$2 (-), MA_ARM_OUT.MP
PROG: R18.2, SW1.2, U1.P$19 (GP14)
RX: U1.P$2 (GP1), U$4.TX
SCK_0: U1.P$24 (GP18), U3.13 (CLK)
SCK_1: U1.P$14 (GP10), U6.6 (CLK), U$3.CLK
SCL: R4.2, U1.P$5 (GP3), U$1.SCL, U$2.SCL
SDA: R3.2, U1.P$4 (GP2), U$1.SDA, U$2.SDA
SERVO1: JP1.1, U1.P$10 (GP7)
SERVO2: JP2.1, U1.P$11 (GP8)
SERVO3: JP3.1, U1.P$6 (GP4)
SERVO4: JP4.1, U1.P$7 (GP5)
SX_BUSY: U1.P$32 (GP27), U3.9 (BUSY)
SX_DIO1: U1.P$29 (GP22), U3.6 (DIO1)
SX_DIO2: U1.P$27 (GP21), U3.5 (DIO2)
SX_RESET: U1.P$31 (GP26), U3.10 (RESET)
TX: U1.P$1 (GP0), U$4.RX
VBUS: U1.P$40 (VBUS)
VCC: 3.3V_REGULATOR.3 (VIN), 5V_REGULATOR.3 (VIN), BATTERY.P$1 (+), C2.2, C4.2, DR_ARM_IN.MP, MA_ARM_IN.MP

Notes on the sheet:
POWER and PYRO
LoRa TELEMETRY
GPS
SENSORS and LOGGING
This is the program switch. When ON, data logging is enabled and liftoff detection is running When OFF, No sensors or logging is running Current drains when PROG is high
Telemetry communicates with pico on SPI0 bus
Data logging components communicate with pico on SPI1 bus
All CS lines have a pullup resistor to initialize all components as inactive If this is not done, garbage values may cause trouble Similarly, all MISO lines are pulled up as they are only used when slave components are in use. They might float otherwise
Push button to reset pico
These headers are used to connect servo motors for actuation in future rockets
MCU and PERIPHERALS

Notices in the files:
parts and their libraries:
SparkFun-Capacitors: Licensing: Creative Commons ShareAlike 4.0 International - https://creativecommons.org/licenses/by-sa/4.0
microbuilder: This work is placed in the public domain, and may be freely used for commercial and non-commercial work with the following conditions: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
